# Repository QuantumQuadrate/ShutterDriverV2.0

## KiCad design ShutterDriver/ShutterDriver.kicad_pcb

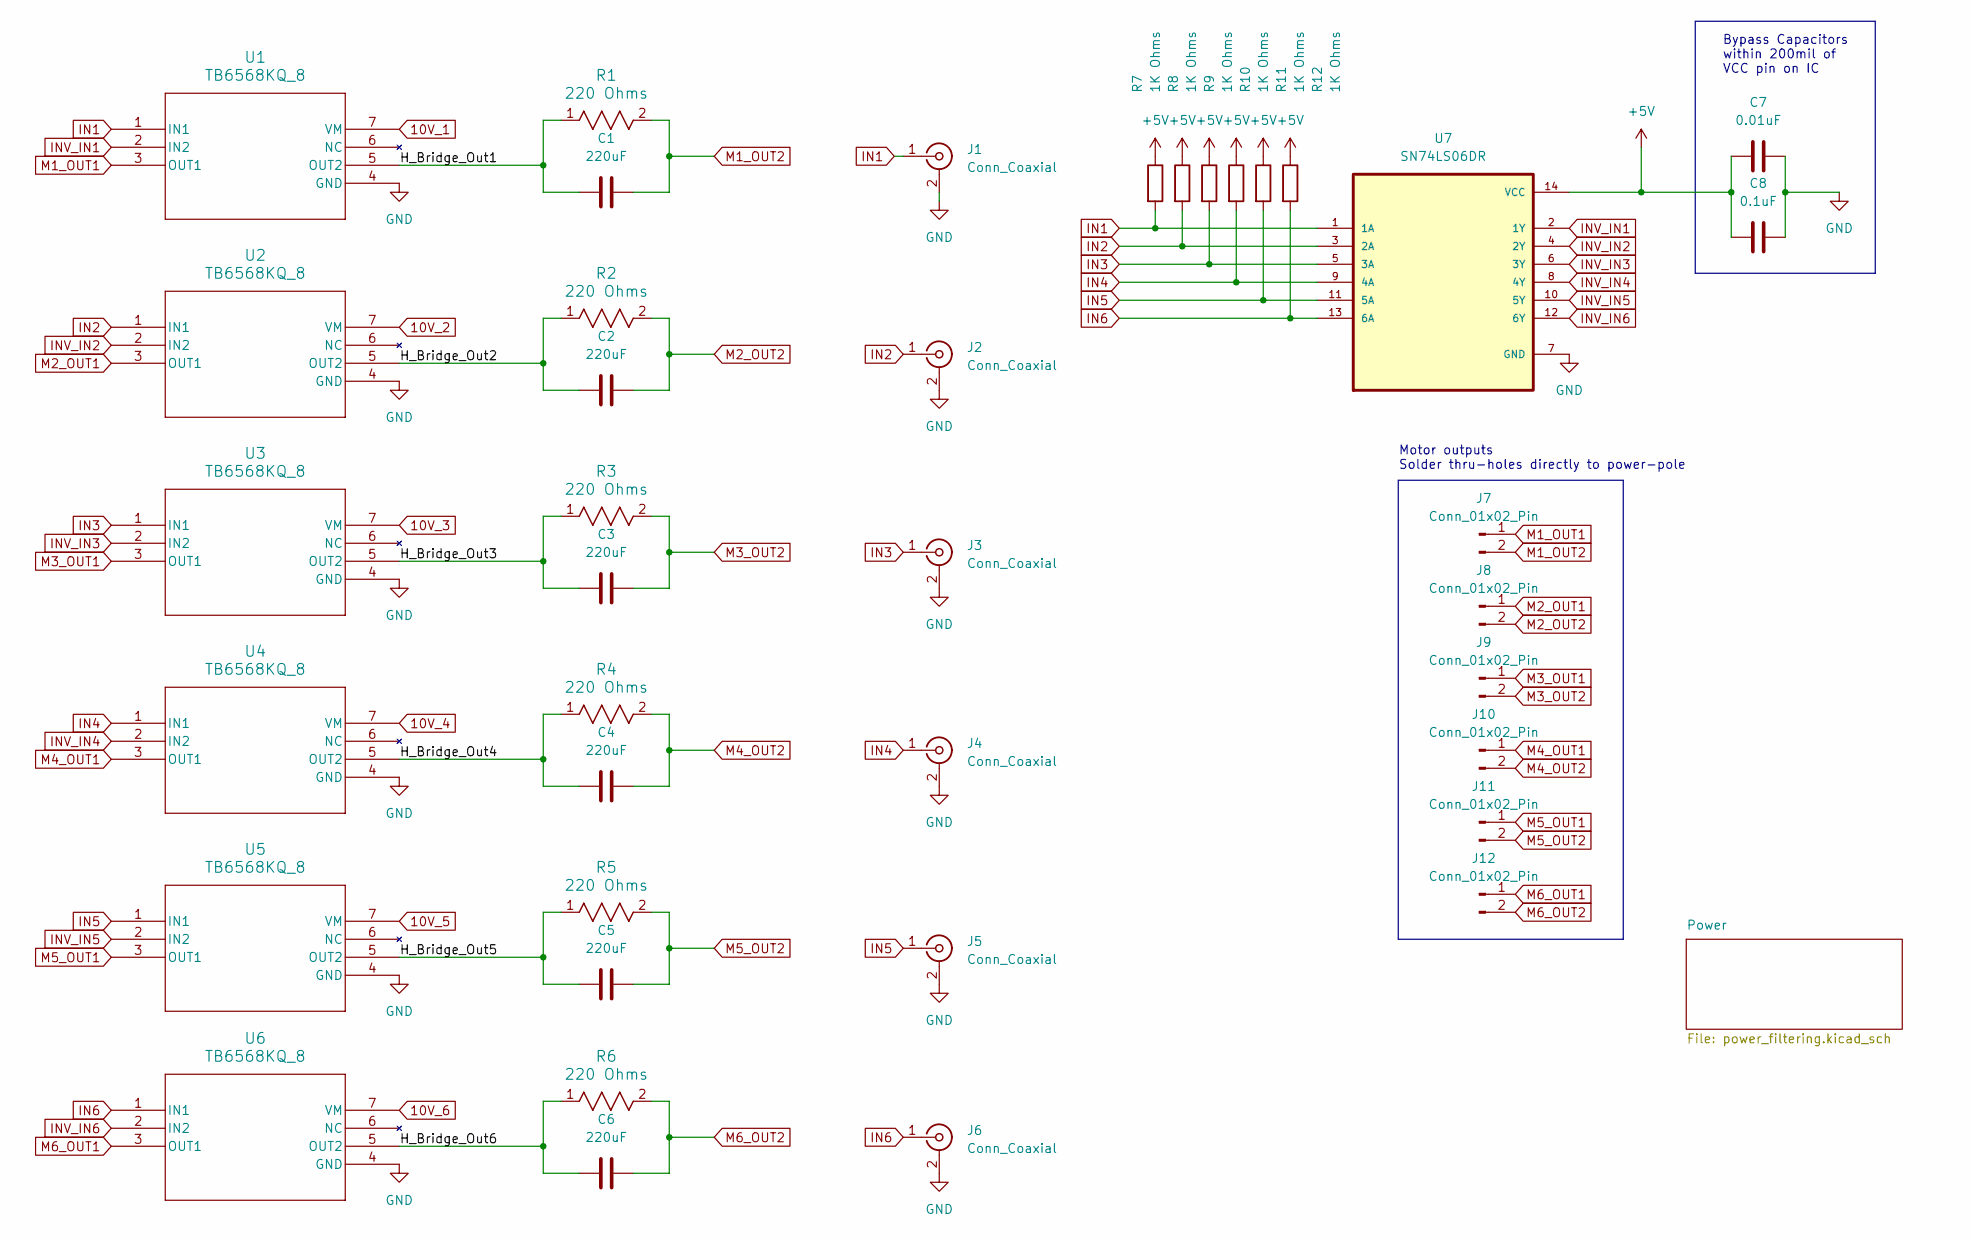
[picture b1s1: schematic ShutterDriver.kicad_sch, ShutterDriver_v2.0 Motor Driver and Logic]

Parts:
C1, C2, C3, C4, C5, C6: 220uF; CP_Radial_D10.0mm_P5.00mm; Part Number ECE-A1EN221U
C7: 0.01uF; C_0805_2012Metric_Pad1.18x1.45mm_HandSolder; Part Number CL21B103KCANNNC
C8: 0.1uF; C_0805_2012Metric_Pad1.18x1.45mm_HandSolder; Part Number CL21B104KCFNNNE
J1, J2, J3, J4, J5, J6: Conn_Coaxial; LINX_CONBNC002; Part Number CONBNC002
J7, J8, J9, J10, J11, J12: Conn_01x02_Pin; Molex_KK-396_A-41791-0002_1x02_P3.96mm_Vertical
R1, R2, R3, R4, R5, R6: 220 Ohms; YAG_FMP200_YAG
R7, R8, R9, R10, R11, R12: 1K Ohms; R_0805_2012Metric_Pad1.20x1.40mm_HandSolder
U1, U2, U3, U4, U5, U6: TB6568KQ_8; HSIP7-P-2p54A_TOS
U7: SN74LS06DR; SOIC127P600X175-14N

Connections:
10V_1: U1.7 (VM); also elsewhere on the board
10V_2: U2.7 (VM); also elsewhere on the board
10V_3: U3.7 (VM); also elsewhere on the board
10V_4: U4.7 (VM); also elsewhere on the board
10V_5: U5.7 (VM); also elsewhere on the board
10V_6: U6.7 (VM); also elsewhere on the board
+5V: C7.1, C8.1, R7.1, R8.1, R9.1, R10.1, R11.1, R12.1, U7.14 (VCC); also elsewhere on the board
/H_Bridge_Out1: C1.1, R1.1, U1.5 (OUT2)
/H_Bridge_Out2: C2.1, R2.1, U2.5 (OUT2)
/H_Bridge_Out3: C3.1, R3.1, U3.5 (OUT2)
/H_Bridge_Out4: C4.1, R4.1, U4.5 (OUT2)
/H_Bridge_Out5: C5.1, R5.1, U5.5 (OUT2)
/H_Bridge_Out6: C6.1, R6.1, U6.5 (OUT2)
GND: C7.2, C8.2, J1.2 (Ext), J2.2 (Ext), J3.2 (Ext), J4.2 (Ext), J5.2 (Ext), J6.2 (Ext), U1.4 (GND), U2.4 (GND), U3.4 (GND), U4.4 (GND), U5.4 (GND), U6.4 (GND), U7.7 (GND); also elsewhere on the board
IN1: J1.1 (In), R11.2, U1.1 (IN1), U7.1 (1A)
IN2: J2.1 (In), R7.2, U2.1 (IN1), U7.3 (2A)
IN3: J3.1 (In), R12.2, U3.1 (IN1), U7.5 (3A)
IN4: J4.1 (In), R9.2, U4.1 (IN1), U7.9 (4A)
IN5: J5.1 (In), R10.2, U5.1 (IN1), U7.11 (5A)
IN6: J6.1 (In), R8.2, U6.1 (IN1), U7.13 (6A)
INV_IN1: U1.2 (IN2), U7.2 (1Y)
INV_IN2: U2.2 (IN2), U7.4 (2Y)
INV_IN3: U3.2 (IN2), U7.6 (3Y)
INV_IN4: U4.2 (IN2), U7.8 (4Y)
INV_IN5: U5.2 (IN2), U7.10 (5Y)
INV_IN6: U6.2 (IN2), U7.12 (6Y)
M1_OUT1: J7.1, U1.3 (OUT1)
M1_OUT2: C1.2, J7.2, R1.2
M2_OUT1: J8.1, U2.3 (OUT1)
M2_OUT2: C2.2, J8.2, R2.2
M3_OUT1: J9.1, U3.3 (OUT1)
M3_OUT2: C3.2, J9.2, R3.2
M4_OUT1: J10.1, U4.3 (OUT1)
M4_OUT2: C4.2, J10.2, R4.2
M5_OUT1: J11.1, U5.3 (OUT1)
M5_OUT2: C5.2, J11.2, R5.2
M6_OUT1: J12.1, U6.3 (OUT1)
M6_OUT2: C6.2, J12.2, R6.2

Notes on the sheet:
Bypass Capacitors within 200mil of VCC pin on IC
Motor outputs Solder thru-holes directly to power-pole

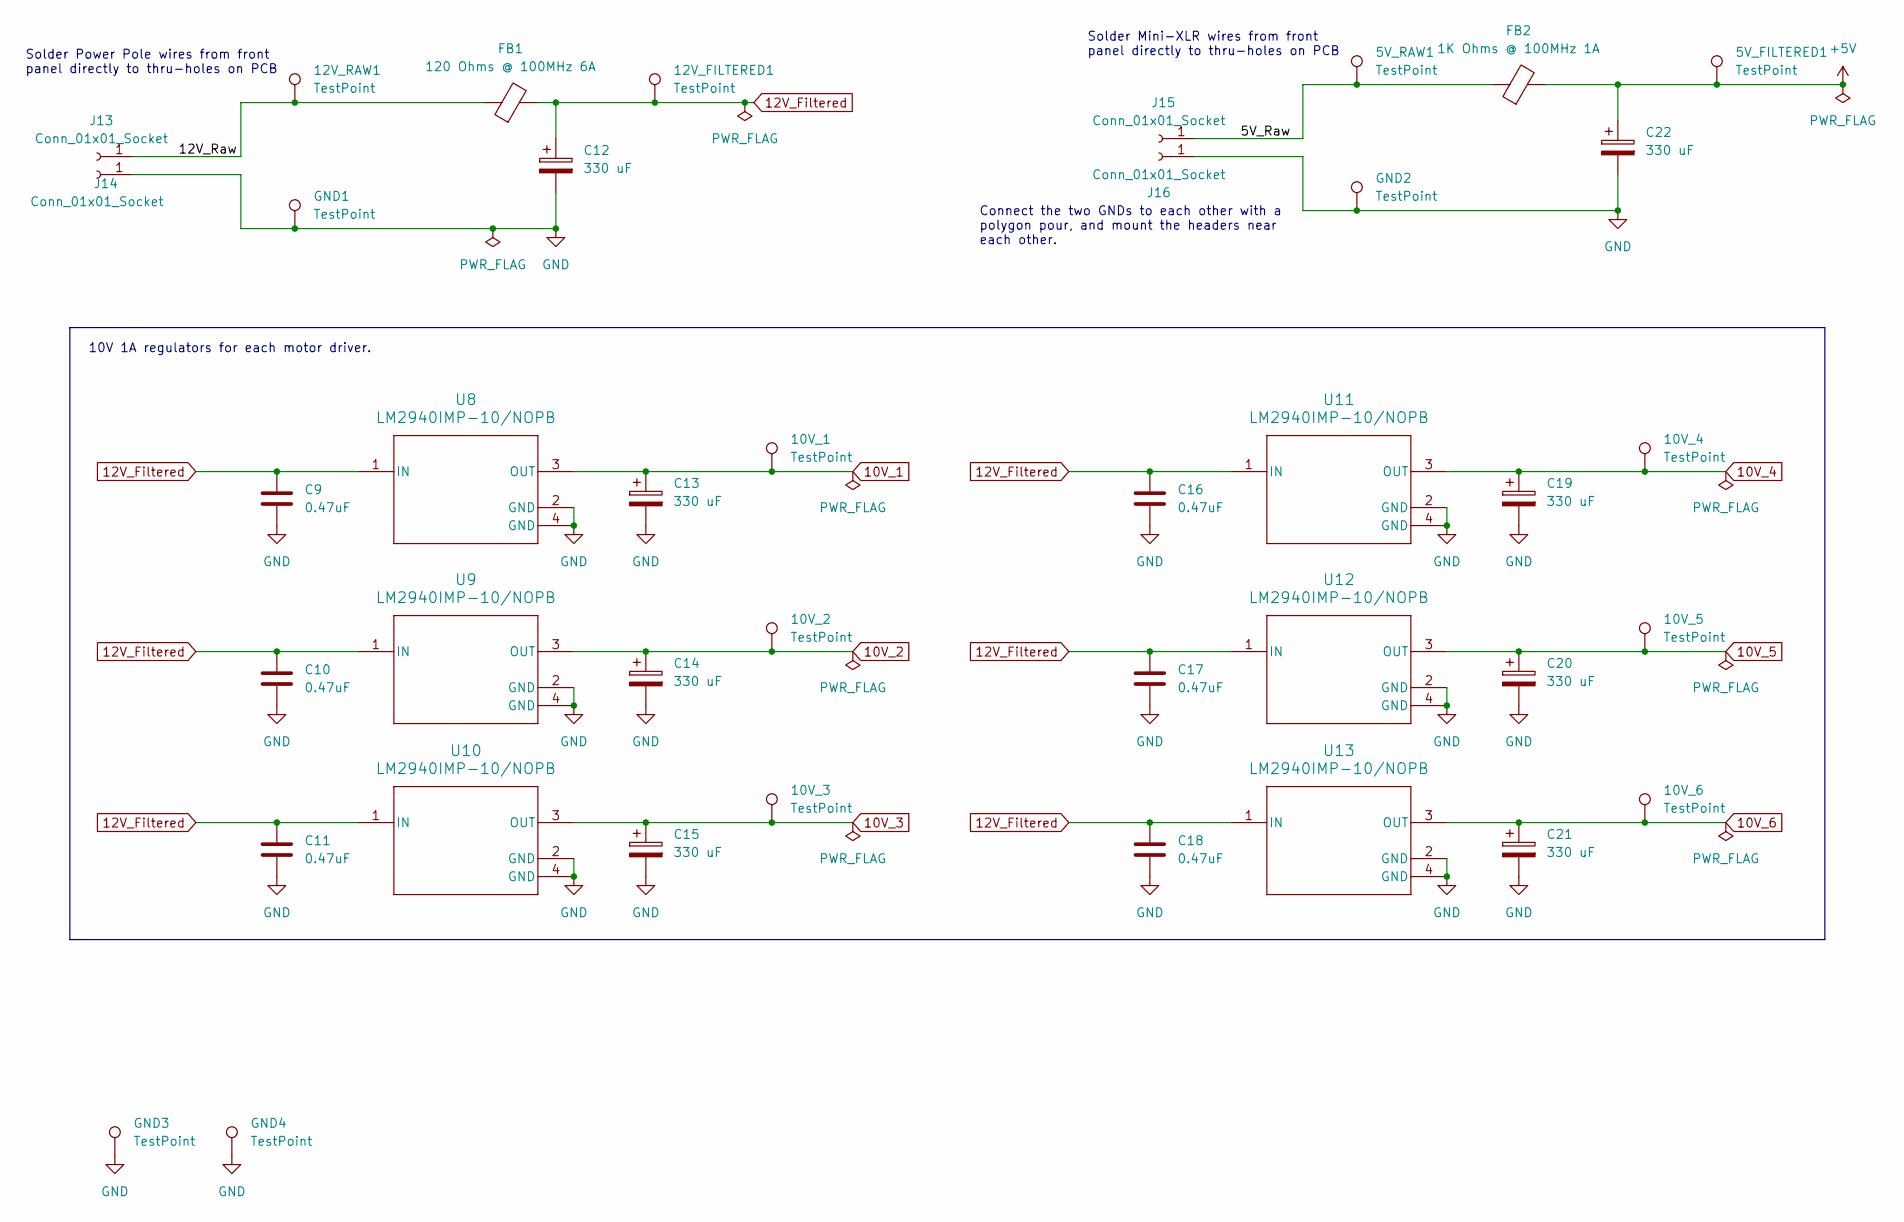
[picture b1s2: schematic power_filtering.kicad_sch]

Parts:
5V_FILTERED1, 5V_RAW1, 10V_1, 10V_2, 10V_3, 10V_4, 10V_5, 10V_6, 12V_FILTERED1, 12V_RAW1: TestPoint; TestPoint_Keystone_5019_Minature
C9, C10, C11, C16, C17, C18: 0.47uF; C_0805_2012Metric_Pad1.18x1.45mm_HandSolder
C12, C13, C14, C15, C19, C20, C21, C22: 330 uF; CP_Elec_8x11.9
FB1: 120 Ohms @ 100MHz 6A; R_0805_2012Metric_Pad1.20x1.40mm_HandSolder
FB2: 1K Ohms @ 100MHz 1A; R_0805_2012Metric_Pad1.20x1.40mm_HandSolder
GND1, GND2, GND3, GND4: TestPoint; TestPoint_Keystone_5019_Minature
J13, J14, J15, J16: Conn_01x01_Socket; Pin_D1.3mm_L11.0mm_LooseFit
U8, U9, U10, U11, U12, U13: LM2940IMP-10/NOPB; DCY0004A_M

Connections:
10V_1: 10V_1.1, C13.1, U8.3 (OUT); also elsewhere on the board
10V_2: 10V_2.1, C14.1, U9.3 (OUT); also elsewhere on the board
10V_3: 10V_3.1, C15.1, U10.3 (OUT); also elsewhere on the board
10V_4: 10V_4.1, C19.1, U11.3 (OUT); also elsewhere on the board
10V_5: 10V_5.1, C20.1, U12.3 (OUT); also elsewhere on the board
10V_6: 10V_6.1, C21.1, U13.3 (OUT); also elsewhere on the board
12V_Filtered: 12V_FILTERED1.1, C9.1, C10.1, C11.1, C12.1, C16.1, C17.1, C18.1, FB1.2, U8.1 (IN), U9.1 (IN), U10.1 (IN), U11.1 (IN), U12.1 (IN), U13.1 (IN)
+5V: 5V_FILTERED1.1, C22.1, FB2.2; also elsewhere on the board
/Power/5V_Raw: 5V_RAW1.1, FB2.1, J15.1
/Power/12V_Raw: 12V_RAW1.1, FB1.1, J13.1
GND: C9.2, C10.2, C11.2, C12.2, C13.2, C14.2, C15.2, C16.2, C17.2, C18.2, C19.2, C20.2, C21.2, C22.2, GND1.1, GND2.1, GND3.1, GND4.1, J14.1, J16.1, U8.2 (GND), U8.4 (GND), U9.2 (GND), U9.4 (GND), U10.2 (GND), U10.4 (GND), U11.2 (GND), U11.4 (GND), U12.2 (GND), U12.4 (GND), U13.2 (GND), U13.4 (GND); also elsewhere on the board

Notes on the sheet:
Solder Mini-XLR wires from front panel directly to thru-holes on PCB
Connect the two GNDs to each other with a polygon pour, and mount the headers near each other.
Solder Power Pole wires from front panel directly to thru-holes on PCB
10V 1A regulators for each motor driver.

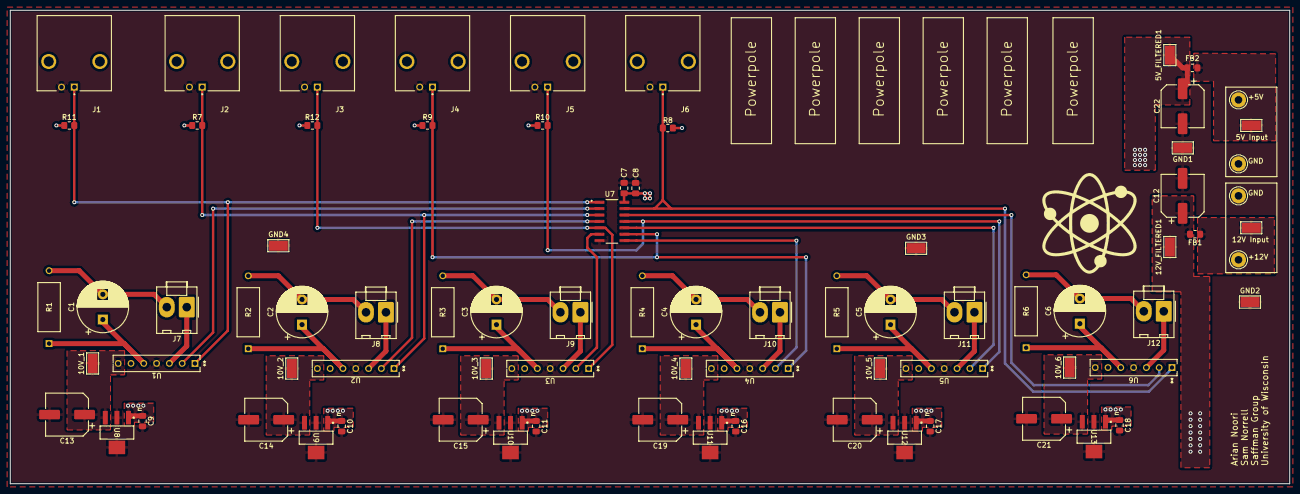
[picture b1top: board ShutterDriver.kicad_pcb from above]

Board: 2 copper layers, 254.0 x 94.0 mm, 79 parts (0 on the bottom side), 41 nets.

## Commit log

2023-12-11 Pushing KiCad files for the ShutterDriver V2.0
